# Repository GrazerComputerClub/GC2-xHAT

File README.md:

# GC2-xHAT
Raspberry Pi Zero Extended HAT for Raspjamming and other Events

## Features

- **7-Segment Display** - 4-Digits TM1637 (Proprietary 2-Wire Bus)  
  CLK  ... GPIO23  
  DIO  ... GPIO24   
- **Sensors**
	 - DHT11/DHT22/AM2302 (Proprietary 1-Wire Bus) - Humidity & Temperature (GPIO22, External Pull-up)
	 - AMD2320/AMD2322 (I2C Bus) - Humidity & Temperature
	 - DS18B20 (1-Wire Bus) - Temperature (GPIO04, External Pull-up)
	 - HC-SR04 (Proprietary Interface) - Distance  
             TRIGGER ... GPIO17  
             ECHO ... GPIO27 (External 5V to 3V divider for input)  
- **Traffic Light** 
	 - LED red (GPIO16, Active High, Default off)
	 - LED yellow/orange (GPIO20, Active High, Default off)
	 - LED green (GPIO21, Active High, Default off)
- **Switches** 
 	 - S1 (GPIO13, Active High, Default Low)
	 - S2 (GPIO19, Active High, Default Low)
	 - S3 (GPIO26, Active High, Default Low)
- **Buzzer** (GPIO18, Active High, Default off) 
- **ATmega 328P Sockel** Programming/Testing  
  RESET ... GPIO25 (Active Low, Default Low with no Power, Default High with Power)  
  MOSI  ... GPIO10  
  MISO  ... GPIO09  
  SCK   ... GPIO11  
- **ESP-01 Sockel** (ESP8266) Programming/Testing  
  RST   ... GPIO06 (Active Low, Default High)  
  GPIO0 ... GPIO12 (High ... Programming, Low ... Flash-Boot, Default Low)  
  TXD   ... GPIO14  
  RXD   ... GPIO15  
- Power Switch for ATmega and ESP-01 (GPIO05, Active Low, Default off)
- HAT EEPROM (I2C Bus)  
	 I2C0, A0-A2 Low

## Assembling

Order recommendation:

- Start with SMD components (FET, EEPROM, resistors)
- ...
- Switches
- 40-pin Header 
- 8-pin Header (need soldering before Buzzer!) 
- Buzzer 
- 14-pin socket 100nF capacitor backside
- 14-pin Socket
- Place electrical tape on backside of 7-seg display
- 7-seg display

Hints: 
- Swiches: Only solder two opposite contacts 
- Standing resistors: Solder short wire first
- Solder R8, R9, R10 lying on backside (to not disturb switches) or
- Advanced people can solder SMD1206 resistors instead of classic standing ones 
- Buzzer can be very loud, solder 47 KOhm resistor for silent operation
- Solder DS18B20 with maximum wire length to keep it away from board heat sources  

### Components list
	
10 x Resistor 470 o. 1K  (LED*: R3, R4, R13, R14 ; Protect: R8, R9, R10, R15, R16, R17)  
 4 x Resistor 4K7 (5V->3V: R1 ; Pull-up: R6, R7 ; Transistor base: R11)  
 1 x Resistor 6K8 (5V->3V: R2)  
 1 x Resistor 47K (Green LED: R5*)  
 3 x Tactile switch 6x6mm (S1, S2, S3)  
 1 x LED red 3mm (LR)  
 1 x LED yellow/orange 3mm (LY)  
 1 x LED green 3mm (YG)  
 1 x LED blue 3mm (LB)  
 1 x LED pink 3mm (LP)  
 1 x Transistor BC547B (T1)  
 1 x Female pin header socket 2x4 (SV2)  
 1 x Female pin header socket 1x4 (U$3)  
 1 x Female pin header socket 2x20 (SV1)  
 1 x 28-Pin DIP-Socket o. 28-Pin ZIF-Socket (0.3''/7.62mm Narrow)  
 1 x DHT11 o. DHT22 o. AM2302 (U$2)  
 1 x AM2322 o. AM2320  (U$4 / U$1)  
 1 x DS18B20 (IC1)  
 1 x TM1637 4 Digi LED display modul (GND, VCC, DIO, CLK)  
 1 x Buzzer (O 12mm, 7.2mm holes) (SG3)  
 1 x FET IRLML6401 (Q1)  
 1 x EEPROM STM M24C64-WMN6 (24C64) **  
 2 x SMD 1206 resistor 3K9 (R18, R19)  
 1 x Capacity 100nF (C1)  
 2 x Spacer 1 cm, M2.5  
 2 x Bolt M2.5

\* Please choose LED resistor corresponding to LED type and 3.3 V, usually 1 KOhm is ok, but our green LED is a low current type, so even 47K makes a satisfying light  
\** Different sizes and manufacturers are possible if EEPROM comply with the Raspberry Pi HAT EEPROM specification (8 bit data, 16 bit address, I2C @ 100 kHz, 3.3 V)

### China-Bezugsquellen Spezialkomponenten:

DHT11, DHT22, AM2320, AM2322, TM1637, Buzzer  
[RoarKit](https://de.aliexpress.com/store/1266255)

### DE-Bezugsquellen Spezialkomponenten:

DHT11: 
* [Reichelt](https://www.reichelt.com/de/en/developer-boards-temperature-humidity-sensor-debo-dht-11-p224221.html) 
* [AZ-Delivery](https://www.az-delivery.de/collections/temperatursensoren/products/5-x-dht11-temperatursensor)  
* [Amazon](https://www.amazon.de/s?k=DHT11)

DHT22: 
* [Reichelt](https://www.reichelt.com/de/en/development-boards-temperature-humidity-sensor-debo-dht-22-p224218.html) 
* [AZ-Delivery](https://www.az-delivery.de/collections/temperatursensoren/products/dht22)   
* [Amazon](https://www.amazon.de/s?k=DHT22)

AM2320: 
* [Amazon](https://www.amazon.de/s?k=AM2320) 

DS18B20: 
* [Reichelt](https://www.reichelt.com/de/en/digital-thermometer-1-wire-0-5-c-to-92-ds-18b20-p58169.html) 
* [AZ-Delivery](https://www.az-delivery.de/collections/temperatursensoren/products/5ersetds18b20)  
* [Amazon](https://www.amazon.de/s?k=18B20)

TM1637: 
* [AZ-Delivery](https://www.az-delivery.de/products/4-digit-display)
* [Amazon](https://www.amazon.de/s?k=TM1637)

Buzzer:
* [Amazon](https://www.amazon.de/s?k=Beeper+5V)

## Case

### Recommanded 3d-printer case for Raspberry Pi B+, 2B, 3B, 3B+ 

[Raspberry Pi case (model B+ / 2 / 3)](https://www.thingiverse.com/thing:559858) by Adrien12  is licensed under the Attribution - Non-Commercial - Share Alike license.
[BY-NC-SA](http://creativecommons.org/licenses/by-nc-sa/3.0/)

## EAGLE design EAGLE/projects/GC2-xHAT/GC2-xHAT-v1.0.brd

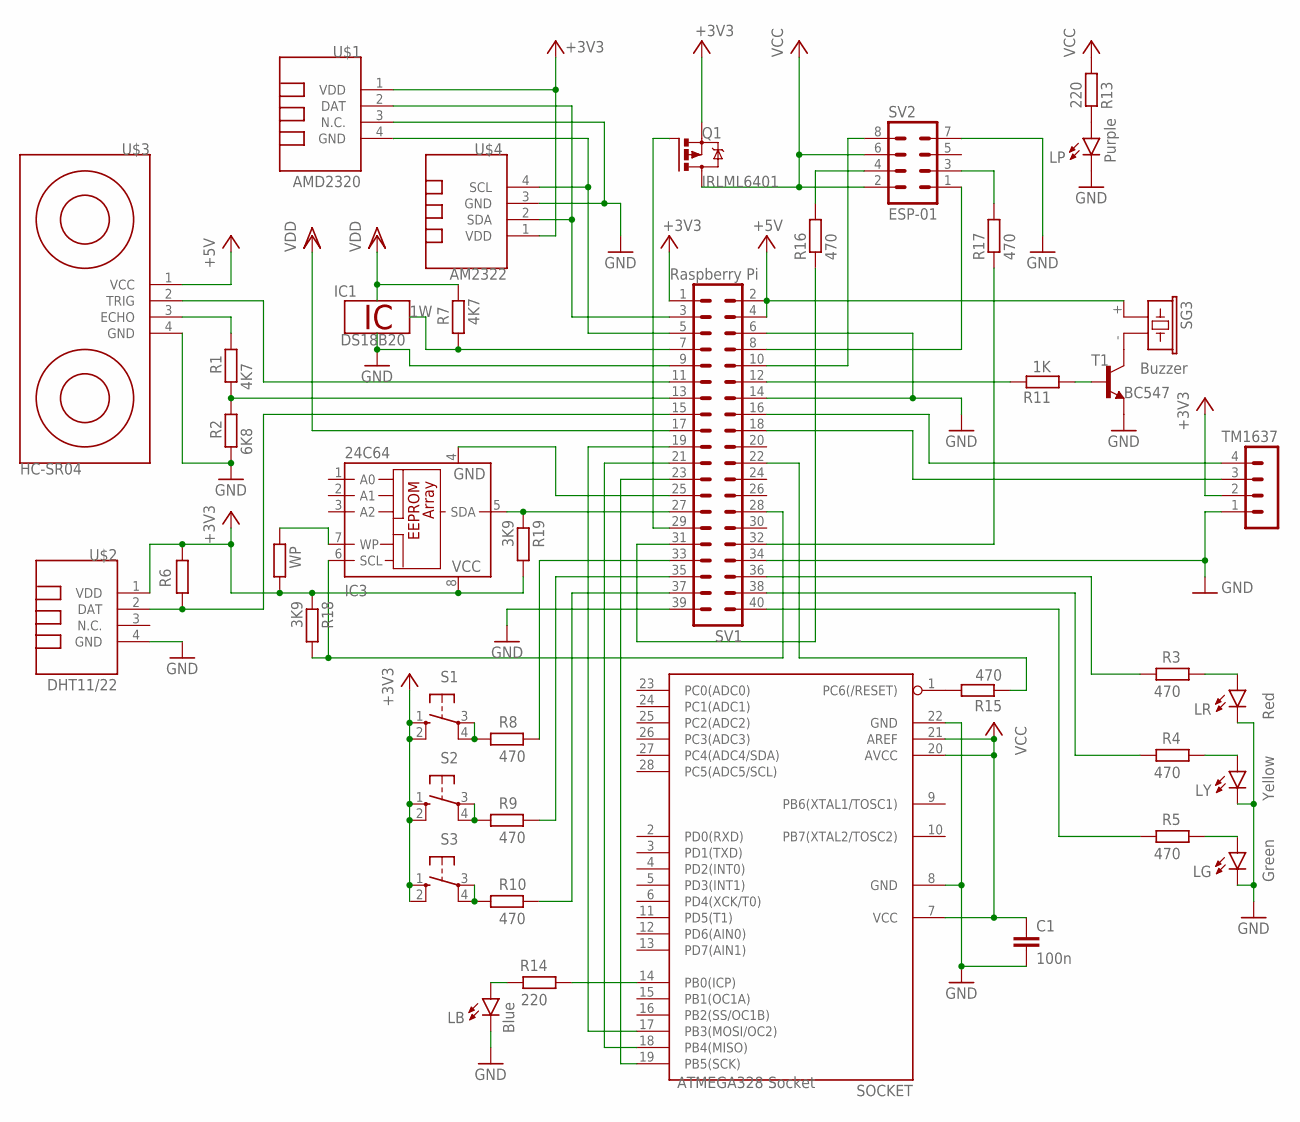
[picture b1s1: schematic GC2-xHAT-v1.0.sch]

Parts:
C1: 100n; C025-024X044
IC1: DS18B20; TO92-
IC3: 24C64; SO-08
LB: Blue; LED3MM
LG: Green; LED3MM
LP: Purple; LED3MM
LR: Red; LED3MM
LY: Yellow; LED3MM
Q1: IRLML6401; MICRO3
R1, R6, R7: 4K7; 0309V
R2: 6K8; 0309V
R3, R4, R5, R8, R9, R10: 470; 0309V
R11: 1K; 0309V
R13, R14: 220; 0309V
R15, R16, R17: 470; 0204/7
R18, R19: 3K9; R1206
S1, S2, S3: 10-XX; B3F-10XX
SG3: Buzzer; F/CM12P
SOCKET: ATMEGA328 Socket; DIL28-3
SV1: Raspberry Pi; MA20-2
SV2: ESP-01; MA04-2
SW: WP; M1406
T1: BC547; TO92
TM1637: MA04-1
U$1: AMD2320; TEMP-HUM-SENSOR-DHT11
U$2: DHT11/22; TEMP-HUM-SENSOR-DHT11
U$3: HC-SR04; ULTRASONIC-HC-SR04#V
U$4: AM2322; TEMP-HUM-SENSOR-AM2322

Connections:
1W: IC1.2 (1W), R7.1, SV1.7
+3V3: IC3.8 (VCC), Q1.2 (S), R6.1, R18.1, R19.2, S1.1 (S), S1.2 (S1), S2.1 (S), S2.2 (S1), S3.1 (S), S3.2 (S1), SV1.1, SW.1, TM1637.2, U$1.1 (VDD), U$2.1 (VDD), U$4.1 (VDD)
+5V: SG3.+ (1), SV1.2, SV1.4, U$3.1 (VCC)
GND: C1.2, IC1.1 (GND), LB.K (C), LG.K (C), LP.K (C), LR.K (C), LY.K (C), R2.1, SOCKET.8 (GND), SOCKET.22 (GND), SV1.6, SV1.9, SV1.14, SV1.34, SV1.39, SV2.7, T1.1 (E), TM1637.1, U$1.3 (N.C.), U$2.4 (GND), U$3.4 (GND), U$4.3 (GND)
unnamed: LY.A, R4.1
unnamed: SV1.3, U$1.2 (DAT), U$4.2 (SDA)
unnamed: SV1.5, U$1.4 (GND), U$4.4 (SCL)
unnamed: R1.1, R2.2, SV1.13
unnamed: R9.1, S2.3, S2.4 (P1)
unnamed: SV1.11, U$3.2 (TRIG)
unnamed: R8.1, S1.3, S1.4 (P1)
unnamed: R11.1, T1.2 (B)
unnamed: R17.2, SV2.3
unnamed: SOCKET.17 (PB3(MOSI/OC2)), SV1.19
unnamed: SOCKET.18 (PB4(MISO)), SV1.21
unnamed: SOCKET.19 (PB5(SCK)), SV1.23
unnamed: LP.A, R13.2
unnamed: LG.A, R5.1
unnamed: R8.2, SV1.33
unnamed: R9.2, SV1.35
unnamed: R10.2, SV1.37
unnamed: R17.1, SV1.32
unnamed: Q1.1 (G), SV1.29
unnamed: R15.2, SOCKET.1 (PC6(/RESET))
unnamed: R14.1, SOCKET.14 (PB0(ICP))
unnamed: R10.1, S3.3, S3.4 (P1)
unnamed: R16.2, SV2.4
unnamed: SV1.8, SV2.1
unnamed: SV1.10, SV2.8
unnamed: R11.2, SV1.12
unnamed: R15.1, SV1.22
unnamed: SV1.16, TM1637.4
unnamed: R6.2, SV1.15, U$2.2 (DAT)
unnamed: LB.A, R14.2
unnamed: IC3.5 (SDA), R19.1, SV1.27
unnamed: IC3.6 (SCL), R18.2, SV1.28
unnamed: R16.1, SV1.31
unnamed: R4.2, SV1.38
unnamed: R3.2, SV1.36
unnamed: LR.A, R3.1
unnamed: SG3.- (2), T1.3 (C)
unnamed: R1.2, U$3.3 (ECHO)
unnamed: SV1.18, TM1637.3
unnamed: IC3.7 (WP), SW.2
unnamed: R5.2, SV1.40
unnamed: IC3.4 (GND), SV1.25
VCC: C1.1, Q1.3 (D), R13.1, SOCKET.7 (VCC), SOCKET.20 (AVCC), SOCKET.21 (AREF), SV2.2, SV2.6
VDD: IC1.3 (VDD), R7.2, SV1.17

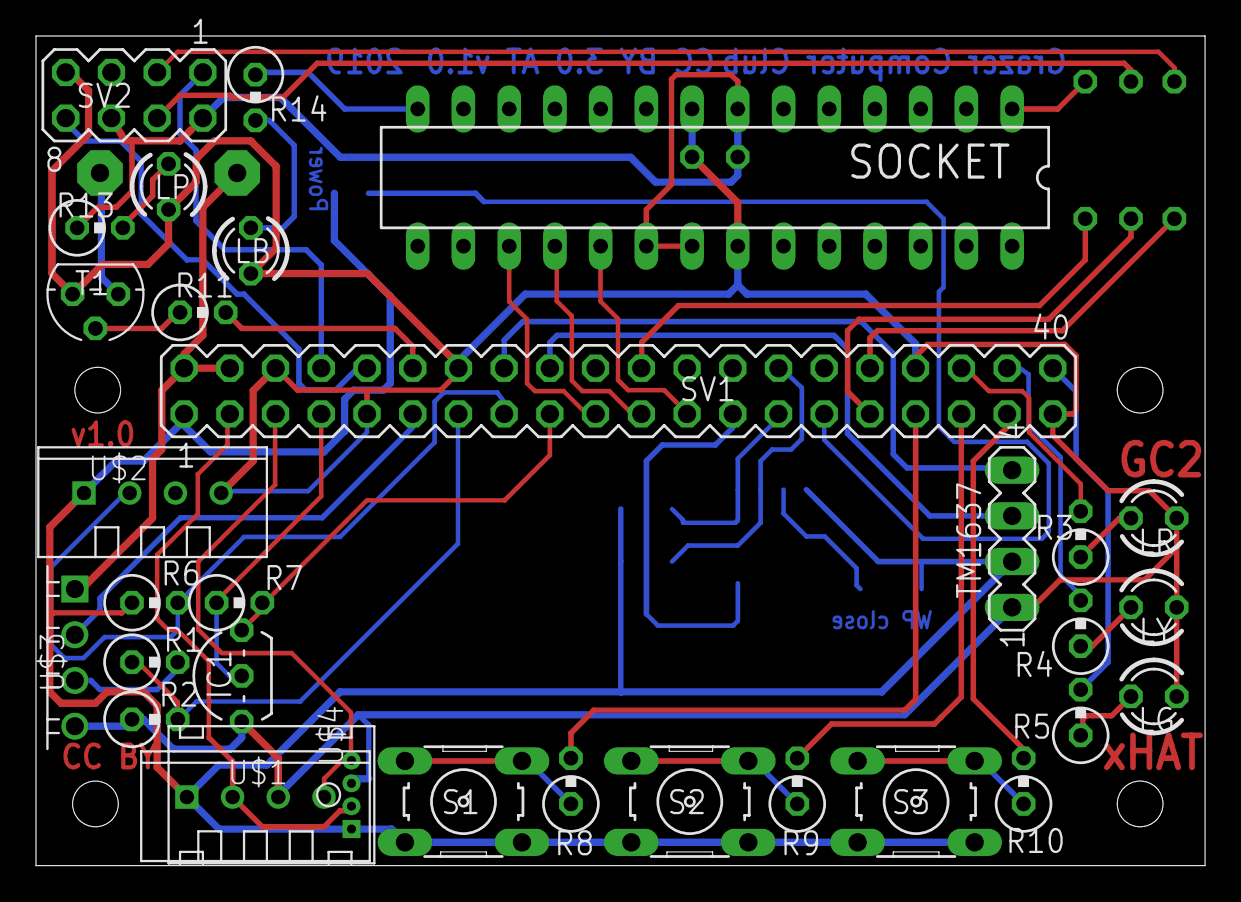
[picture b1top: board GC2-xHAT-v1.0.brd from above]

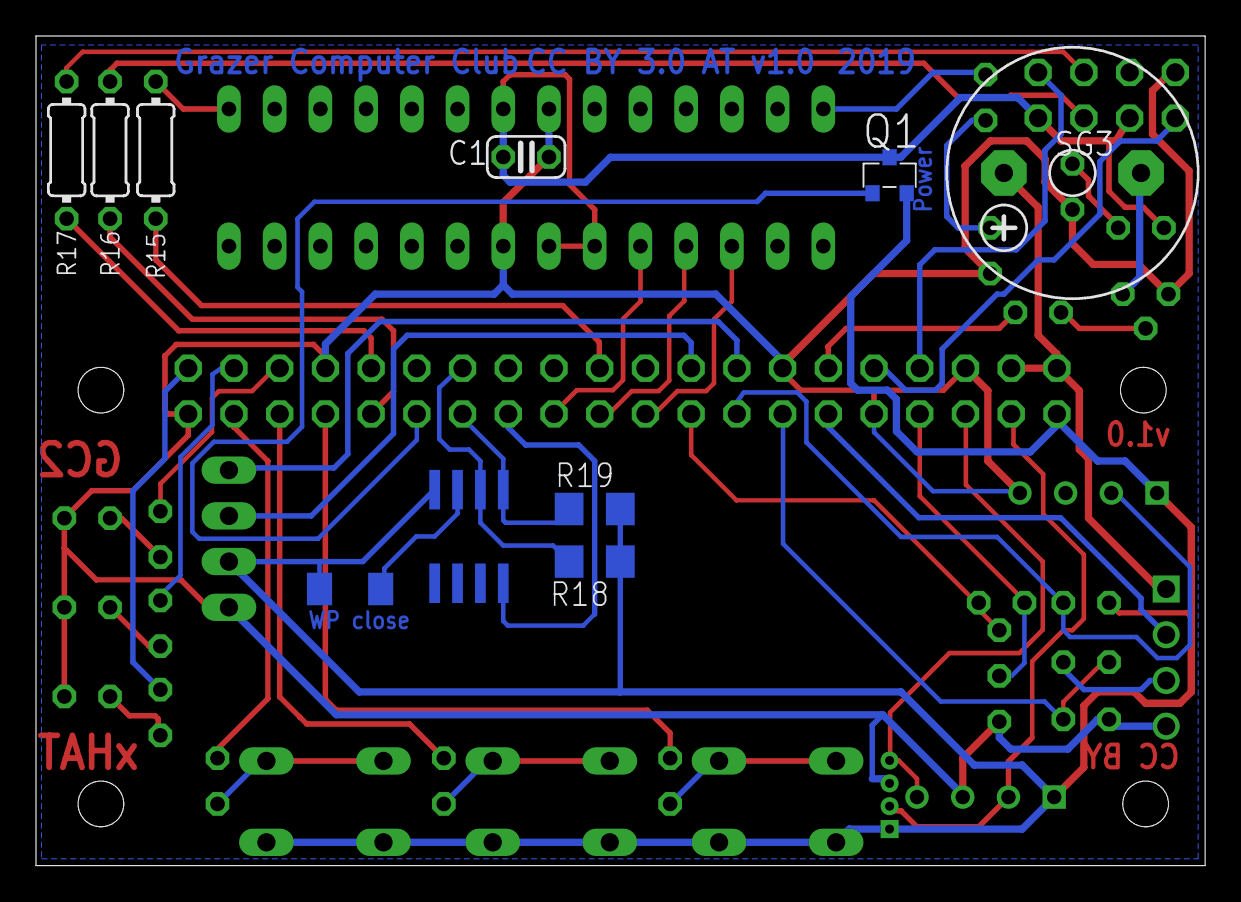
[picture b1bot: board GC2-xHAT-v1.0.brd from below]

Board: 2 copper layers, 64.9 x 46.1 mm, 41 parts (10 on the bottom side), 48 nets.

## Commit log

2019-02-27 Eagle PCB Design Version 1.0
2019-02-27 Create Licence
2019-04-21 HAT EEPROM
2019-04-29 ESP01 fix & German aliases
2019-04-29 8k blank file for erase
2019-05-02 product_uuid random
2019-05-04 ESP commands
2019-07-28 typo
2020-05-03 TonalBuzzer sample
2020-06-05 Banana Pi atpoweroff not working

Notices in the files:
EAGLE/projects/GC2-xHAT/GC2-xHAT-v1.0.brd:
CC BY
CC BY 3.0 AT
parts and their libraries:
diy-modules: Released under the Creative Commons Attribution 4.0 International License: http://creativecommons.org/licenses/by/4.0
